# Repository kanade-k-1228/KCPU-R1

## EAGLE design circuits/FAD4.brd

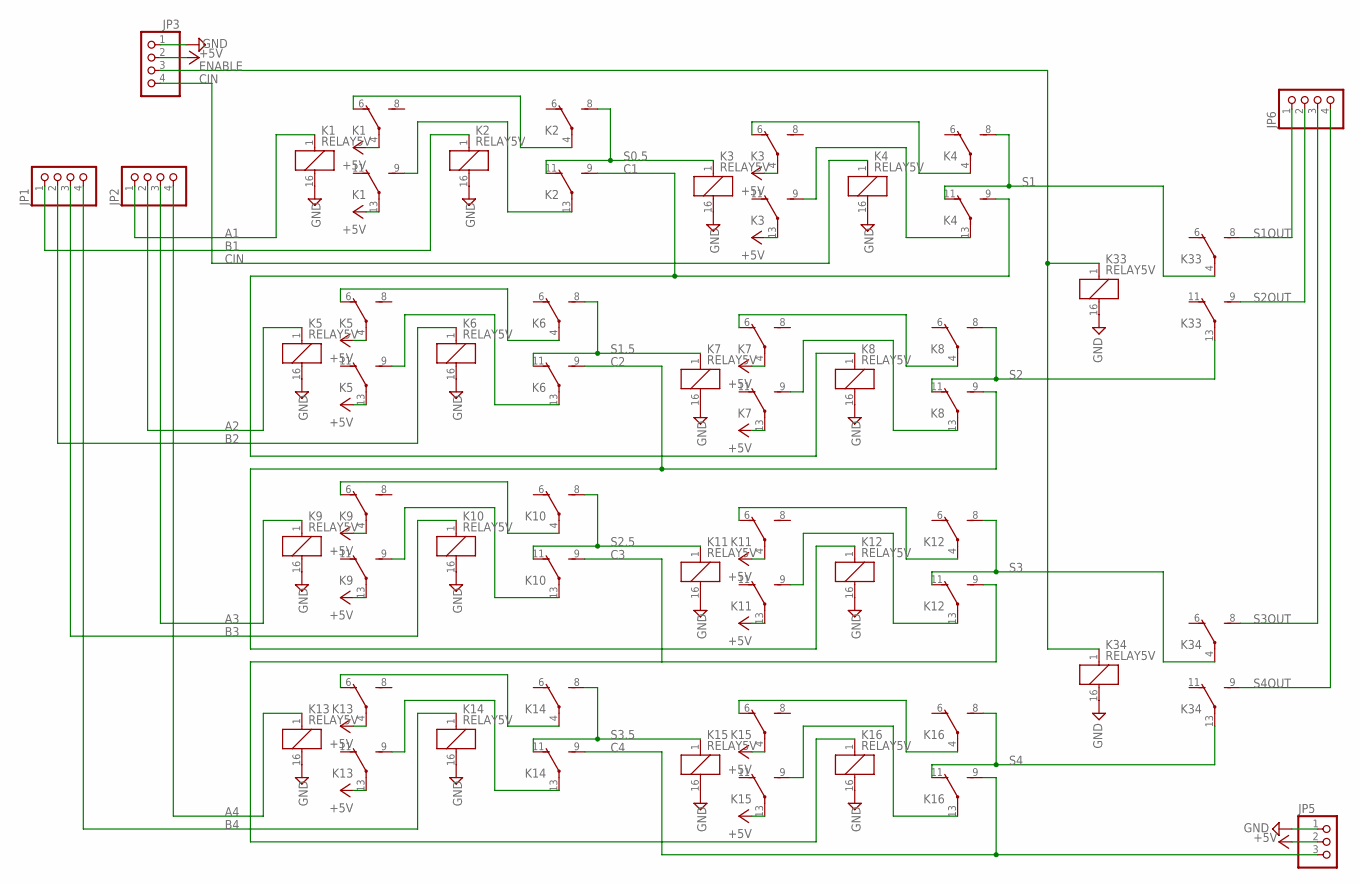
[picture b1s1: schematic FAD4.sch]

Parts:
JP1, JP2, JP3, JP6: PINHD-1X4; 1X04
JP5: PINHD-1X3; 1X03
K1, K2, K3, K4, K5, K6, K7, K8, K9, K10, K11, K12, K13, K14, K15, K16, K33, K34: RELAY5V; DS-BT

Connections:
+5V: JP3.2, JP5.2, K1.4, K1.13, K3.4, K3.13, K5.4, K5.13, K7.4, K7.13, K9.4, K9.13, K11.4, K11.13, K13.4, K13.13, K15.4, K15.13
A1: JP2.1, K1.1 (+)
A2: JP2.2, K5.1 (+)
A3: JP2.3, K9.1 (+)
A4: JP2.4, K13.1 (+)
B1: JP1.1, K2.1 (+)
B2: JP1.2, K6.1 (+)
B3: JP1.3, K10.1 (+)
B4: JP1.4, K14.1 (+)
C1: K2.9 (S), K4.9 (S), K8.1 (+)
C2: K6.9 (S), K8.9 (S), K12.1 (+)
C3: K10.9 (S), K12.9 (S), K16.1 (+)
C4: JP5.3, K14.9 (S), K16.9 (S)
CIN: JP3.4, K4.1 (+)
ENABLE: JP3.3, K33.1 (+), K34.1 (+)
GND: JP3.1, JP5.1, K1.16 (-), K2.16 (-), K3.16 (-), K4.16 (-), K5.16 (-), K6.16 (-), K7.16 (-), K8.16 (-), K9.16 (-), K10.16 (-), K11.16 (-), K12.16 (-), K13.16 (-), K14.16 (-), K15.16 (-), K16.16 (-), K33.16 (-), K34.16 (-)
unnamed: K3.9 (S), K4.13
unnamed: K1.9 (S), K2.13
unnamed: K1.6 (O), K2.4
unnamed: K3.6 (O), K4.4
unnamed: K5.9 (S), K6.13
unnamed: K5.6 (O), K6.4
unnamed: K7.9 (S), K8.13
unnamed: K7.6 (O), K8.4
unnamed: K9.9 (S), K10.13
unnamed: K9.6 (O), K10.4
unnamed: K11.9 (S), K12.13
unnamed: K11.6 (O), K12.4
unnamed: K13.9 (S), K14.13
unnamed: K13.6 (O), K14.4
unnamed: K15.9 (S), K16.13
unnamed: K15.6 (O), K16.4
S0.5: K2.8 (S), K2.11 (O), K3.1 (+)
S1: K4.8 (S), K4.11 (O), K33.4
S1.5: K6.8 (S), K6.11 (O), K7.1 (+)
S1OUT: JP6.1, K33.8 (S)
S2: K8.8 (S), K8.11 (O), K33.13
S2.5: K10.8 (S), K10.11 (O), K11.1 (+)
S2OUT: JP6.2, K33.9 (S)
S3: K12.8 (S), K12.11 (O), K34.4
S3.5: K14.8 (S), K14.11 (O), K15.1 (+)
S3OUT: JP6.3, K34.8 (S)
S4: K16.8 (S), K16.11 (O), K34.13
S4OUT: JP6.4, K34.9 (S)

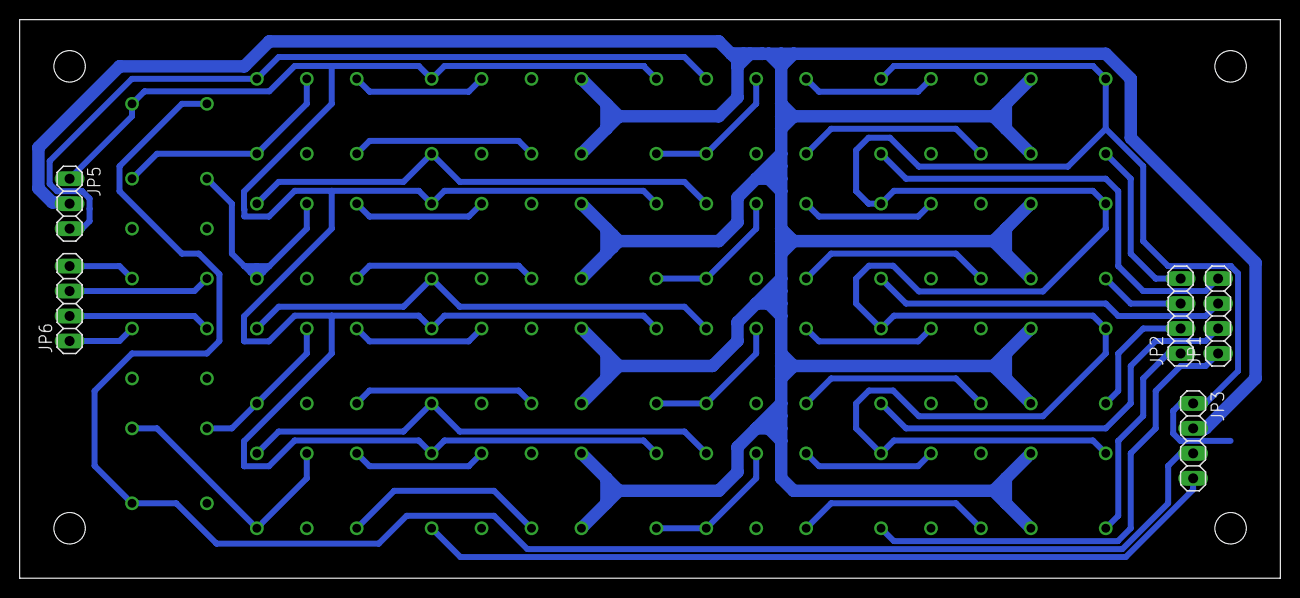
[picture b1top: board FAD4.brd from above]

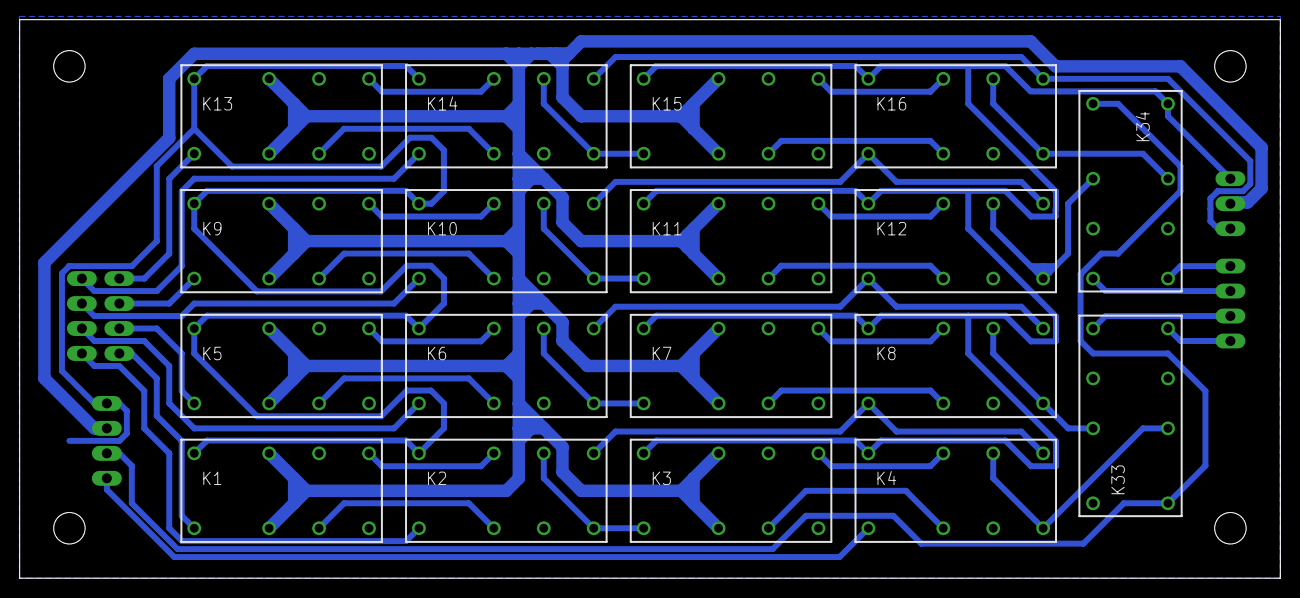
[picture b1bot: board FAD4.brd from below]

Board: 2 copper layers, 128.2 x 56.8 mm, 27 parts (18 on the bottom side), 44 nets.

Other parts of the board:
U$1, U$2, U$3, U$4: HOLE_3.2

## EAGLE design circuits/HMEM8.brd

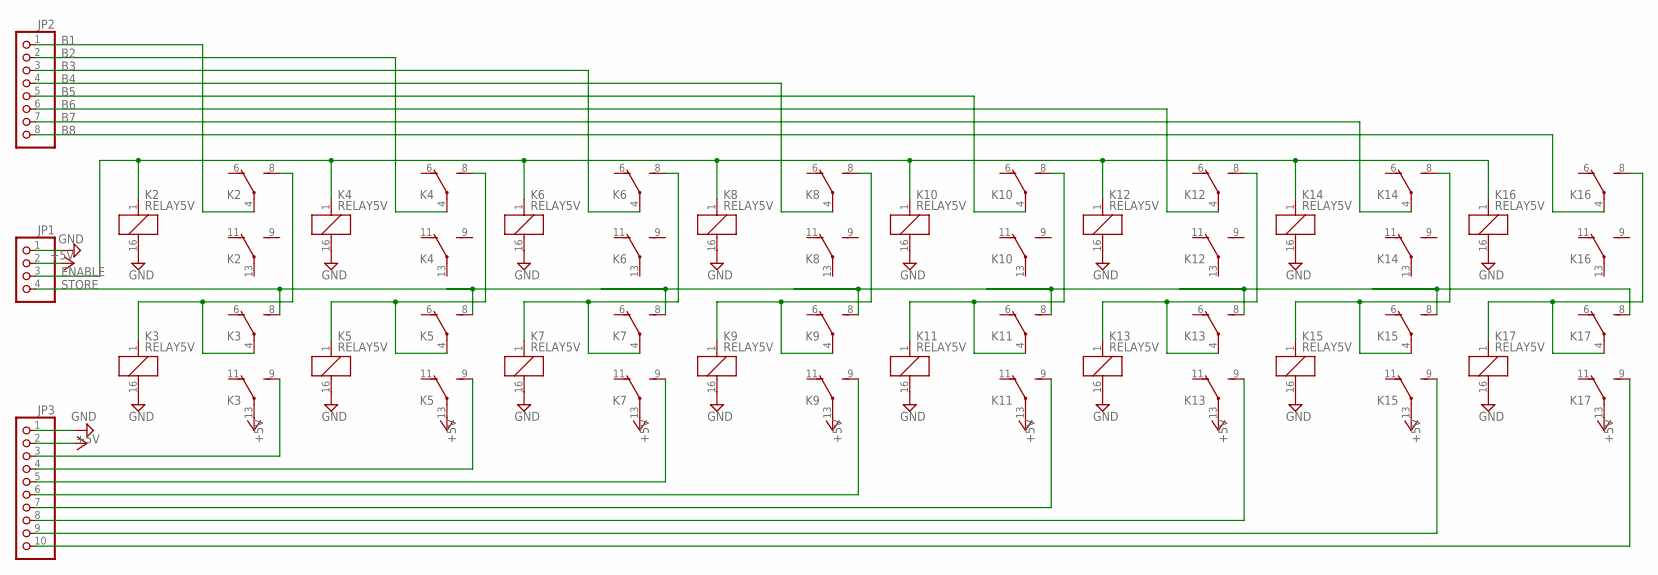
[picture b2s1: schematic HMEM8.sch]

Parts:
JP1: PINHD-1X4; 1X04
JP2: PINHD-1X8; 1X08
JP3: PINHD-1X10; 1X10
K2, K3, K4, K5, K6, K7, K8, K9, K10, K11, K12, K13, K14, K15, K16, K17: RELAY5V; DS-BT

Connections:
+5V: JP1.2, JP3.2, K3.13, K5.13, K7.13, K9.13, K11.13, K13.13, K15.13, K17.13
B1: JP2.1, K2.4
B2: JP2.2, K4.4
B3: JP2.3, K6.4
B4: JP2.4, K8.4
B5: JP2.5, K10.4
B6: JP2.6, K12.4
B7: JP2.7, K14.4
B8: JP2.8, K16.4
ENABLE: JP1.3, K2.1 (+), K4.1 (+), K6.1 (+), K8.1 (+), K10.1 (+), K12.1 (+), K14.1 (+), K16.1 (+)
GND: JP1.1, JP3.1, K2.16 (-), K3.16 (-), K4.16 (-), K5.16 (-), K6.16 (-), K7.16 (-), K8.16 (-), K9.16 (-), K10.16 (-), K11.16 (-), K12.16 (-), K13.16 (-), K14.16 (-), K15.16 (-), K16.16 (-), K17.16 (-)
unnamed: K2.8 (S), K3.1 (+), K3.4
unnamed: JP3.3, K3.9 (S)
unnamed: K4.8 (S), K5.1 (+), K5.4
unnamed: K6.8 (S), K7.1 (+), K7.4
unnamed: K8.8 (S), K9.1 (+), K9.4
unnamed: JP3.4, K5.9 (S)
unnamed: K10.8 (S), K11.1 (+), K11.4
unnamed: JP3.5, K7.9 (S)
unnamed: K12.8 (S), K13.1 (+), K13.4
unnamed: JP3.6, K9.9 (S)
unnamed: K14.8 (S), K15.1 (+), K15.4
unnamed: JP3.7, K11.9 (S)
unnamed: K16.8 (S), K17.1 (+), K17.4
unnamed: JP3.8, K13.9 (S)
unnamed: JP3.9, K15.9 (S)
unnamed: JP3.10, K17.9 (S)
STORE: JP1.4, K3.8 (S), K5.8 (S), K7.8 (S), K9.8 (S), K11.8 (S), K13.8 (S), K15.8 (S), K17.8 (S)

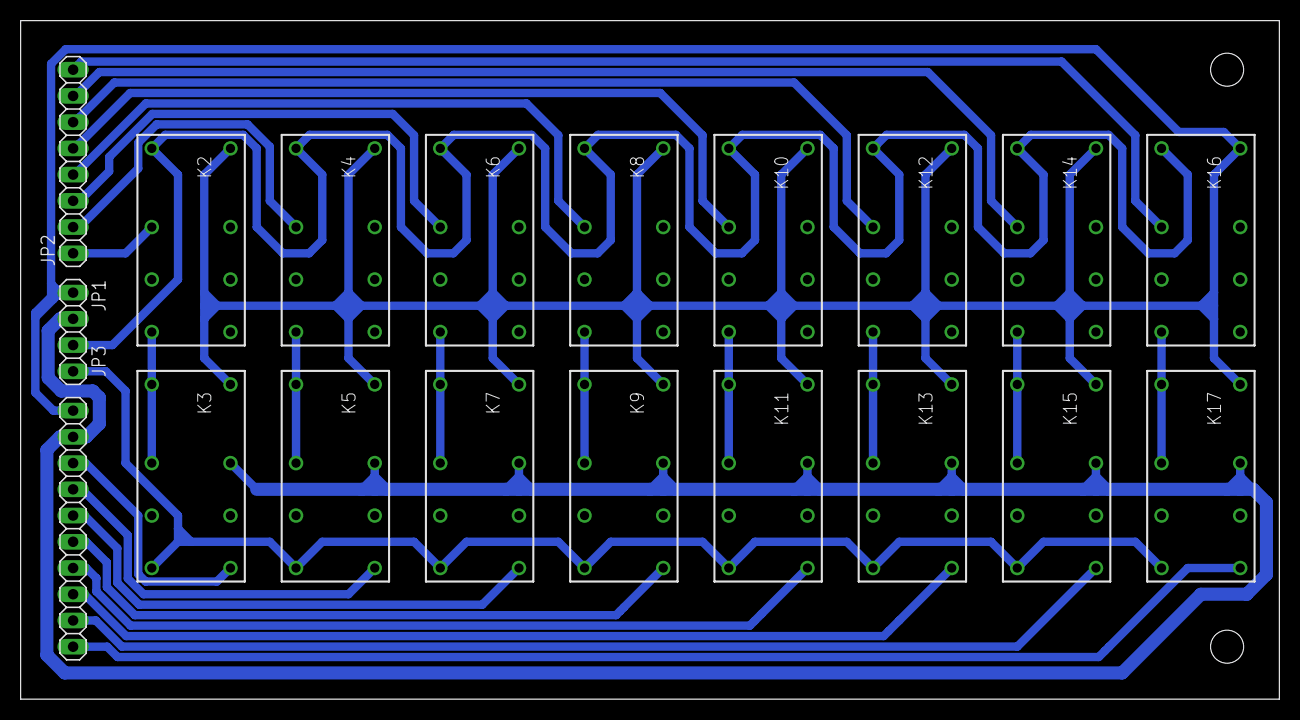
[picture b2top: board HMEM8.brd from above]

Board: 2 copper layers, 121.9 x 65.7 mm, 21 parts (0 on the bottom side), 28 nets.

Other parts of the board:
U$1, U$2: HOLE_3.2

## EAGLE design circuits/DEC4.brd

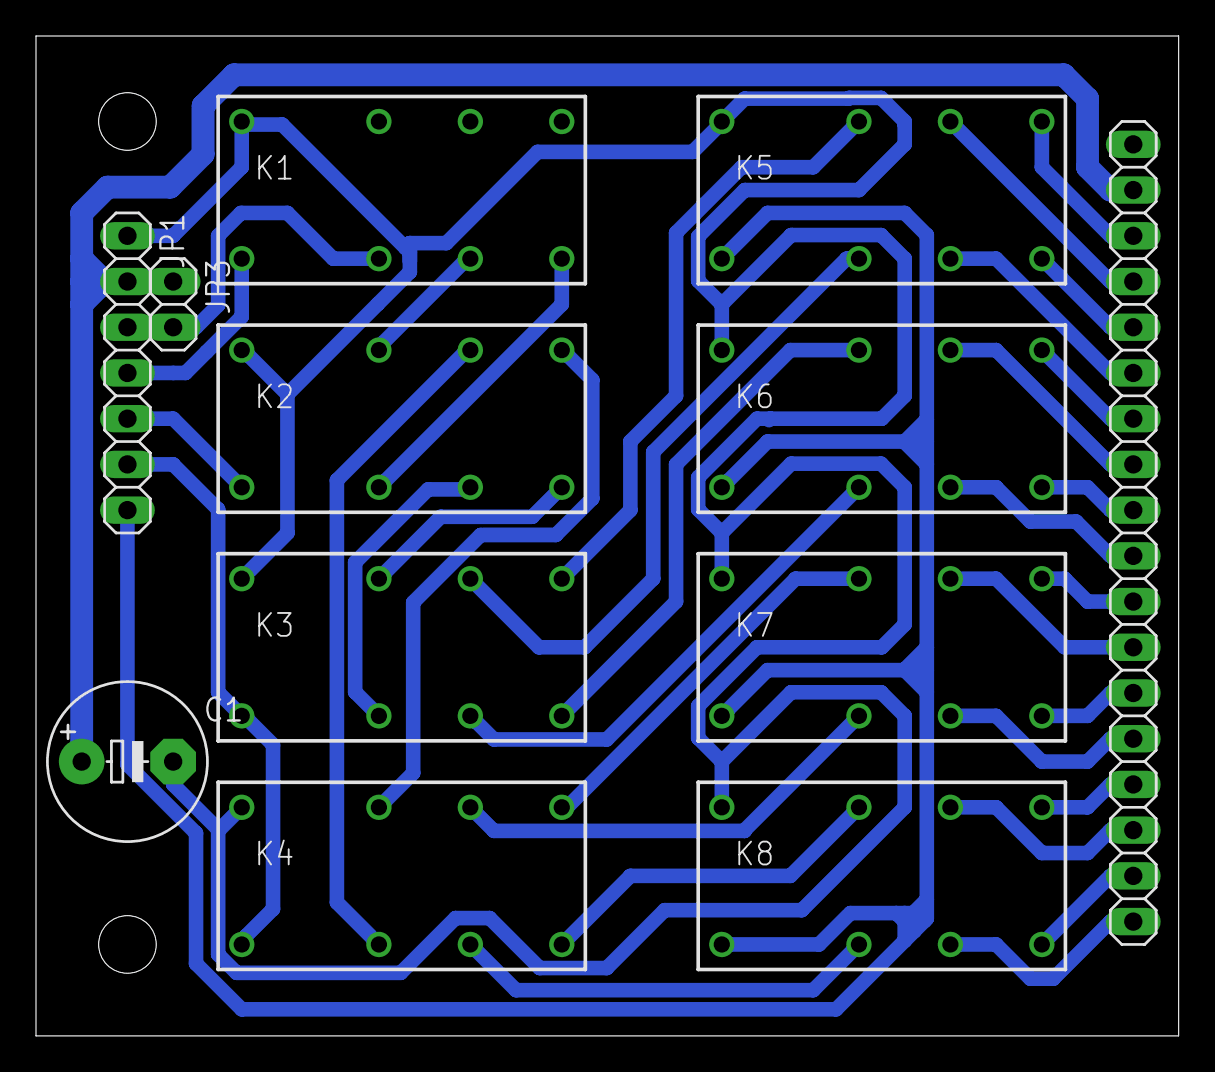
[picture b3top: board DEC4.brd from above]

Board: 2 copper layers, 63.5 x 55.5 mm, 14 parts (0 on the bottom side), 37 nets.

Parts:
C1: E5-8,5
JP1: 1X07
JP2: 1X18
JP3: 1X02
K1, K2, K3, K4, K5, K6, K7, K8: RELAY5V; DS-BT
U$1, U$2: HOLE_3.2

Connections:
+5V: C1.+, JP1.2, JP2.2, JP3.1
GND: C1.-, JP1.1, JP2.1, K1.16, K2.16, K3.16, K4.16, K5.16, K6.16, K7.16, K8.16
unnamed: K1.8, K2.4
unnamed: K1.6, K2.13
unnamed: K2.8, K3.13
unnamed: K2.6, K3.4
unnamed: K2.9, K4.13
unnamed: K2.11, K4.4
unnamed: K3.9, K5.13
unnamed: K3.11, K5.4
unnamed: K3.8, K6.13
unnamed: K3.6, K6.4
unnamed: K4.9, K7.13
unnamed: K4.11, K7.4
unnamed: K4.8, K8.13
unnamed: K4.6, K8.4
unnamed: JP2.3, K5.9
unnamed: JP1.6, K3.1, K4.1
unnamed: JP1.7, K5.1, K6.1, K7.1, K8.1
unnamed: JP2.4, K5.11
unnamed: JP1.4, K1.1
unnamed: JP1.5, K2.1
unnamed: JP2.5, K5.8
unnamed: JP2.6, K5.6
unnamed: JP2.7, K6.9
unnamed: JP2.8, K6.11
unnamed: JP2.9, K6.8
unnamed: JP2.10, K6.6
unnamed: JP2.11, K7.9
unnamed: JP2.12, K7.11
unnamed: JP2.13, K7.8
unnamed: JP2.14, K7.6
unnamed: JP2.15, K8.9
unnamed: JP2.16, K8.11
unnamed: JP2.17, K8.8
unnamed: JP2.18, K8.6
unnamed: JP1.3, JP3.2, K1.4

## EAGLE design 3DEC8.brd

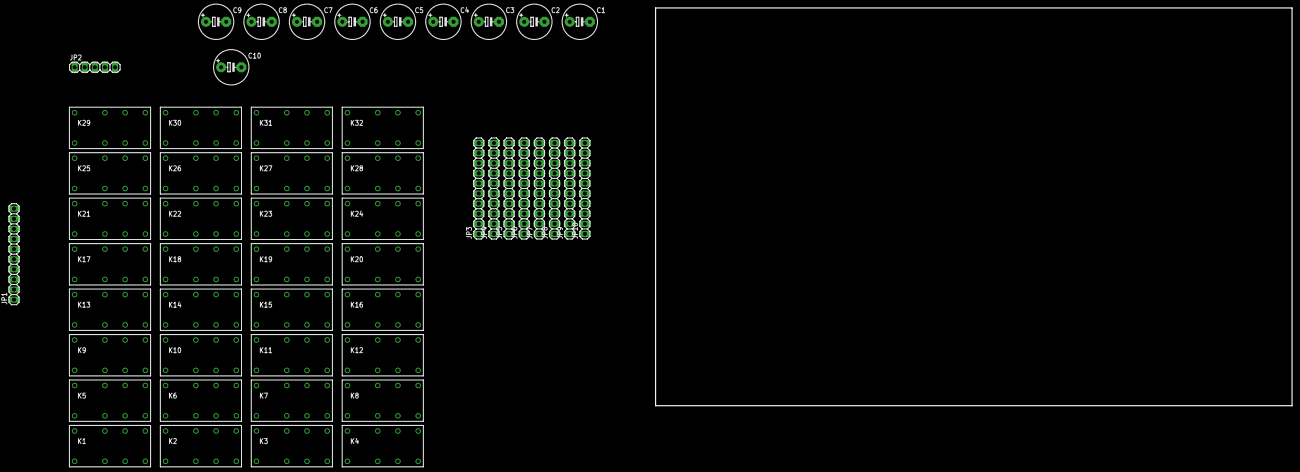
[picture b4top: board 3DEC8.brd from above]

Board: 2 copper layers, 160.0 x 100.0 mm, 52 parts (0 on the bottom side), 87 nets, no tracks yet.

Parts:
C1, C2, C3, C4, C5, C6, C7, C8, C9, C10: E5-8,5
JP1, JP3, JP4, JP5, JP6, JP7, JP8, JP9, JP10: 1X10
JP2: 1X05
K1, K2, K3, K4, K5, K6, K7, K8, K9, K10, K11, K12, K13, K14, K15, K16, K17, K18, K19, K20, K21, K22, K23, K24, K25, K26, K27, K28, K29, K30, K31, K32: RELAY5V; DS-BT

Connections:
+5V: C1.+, C2.+, C3.+, C4.+, C5.+, C6.+, C7.+, C8.+, C9.+, C10.+, JP1.2, JP2.2, JP3.2, JP4.2, JP5.2, JP6.2, JP7.2, JP8.2, JP9.2, JP10.2
GND: C1.-, C2.-, C3.-, C4.-, C5.-, C6.-, C7.-, C8.-, C9.-, C10.-, JP1.1, JP2.1, JP3.1, JP4.1, JP5.1, JP6.1, JP7.1, JP8.1, JP9.1, JP10.1, K1.16, K2.16, K3.16, K4.16, K5.16, K6.16, K7.16, K8.16, K9.16, K10.16, K11.16, K12.16, K13.16, K14.16, K15.16, K16.16, K17.16, K18.16, K19.16, K20.16, K21.16, K22.16, K23.16, K24.16, K25.16, K26.16, K27.16, K28.16, K29.16, K30.16, K31.16, K32.16
unnamed: K1.8, K2.4
unnamed: K1.6, K2.13
unnamed: K2.8, K3.13
unnamed: K2.6, K3.4
unnamed: K2.9, K4.13
unnamed: K2.11, K4.4
unnamed: JP10.3, K3.9
unnamed: K5.8, K6.4
unnamed: JP9.3, K3.11
unnamed: JP7.3, K3.6
unnamed: K5.6, K6.13
unnamed: JP5.3, K4.11
unnamed: JP4.4, K8.8
unnamed: JP4.3, K4.8
unnamed: JP8.3, K3.8
unnamed: JP4.5, K12.8
unnamed: JP6.3, K4.9
unnamed: K6.8, K7.13
unnamed: JP2.3, K1.1, K5.1, K9.1, K13.1, K17.1, K21.1, K25.1, K29.1
unnamed: JP2.4, K2.1, K6.1, K10.1, K14.1, K18.1, K22.1, K26.1, K30.1
unnamed: K6.6, K7.4
unnamed: K6.9, K8.13
unnamed: K6.11, K8.4
unnamed: JP7.4, K7.6
unnamed: JP5.4, K8.11
unnamed: JP3.4, K8.6
unnamed: JP1.4, K5.4
unnamed: JP9.4, K7.11
unnamed: JP3.3, K4.6
unnamed: JP8.4, K7.8
unnamed: JP6.4, K8.9
unnamed: JP1.3, K1.4
unnamed: JP10.4, K7.9
unnamed: K9.8, K10.4
unnamed: K9.6, K10.13
unnamed: K10.8, K11.13
unnamed: K10.6, K11.4
unnamed: K10.9, K12.13
unnamed: K10.11, K12.4
unnamed: JP7.5, K11.6
unnamed: JP5.5, K12.11
unnamed: JP3.5, K12.6
unnamed: JP2.5, K3.1, K4.1, K7.1, K8.1, K11.1, K12.1, K15.1, K16.1, K19.1, K20.1, K23.1, K24.1, K27.1, K28.1, K31.1, K32.1
unnamed: JP1.5, K9.4
unnamed: JP6.5, K12.9
unnamed: K13.8, K14.4
unnamed: K13.6, K14.13
unnamed: K14.8, K15.13
unnamed: K14.6, K15.4
unnamed: K14.9, K16.13
unnamed: K14.11, K16.4
unnamed: JP3.6, K16.6
unnamed: JP1.6, K13.4
unnamed: K17.8, K18.4
unnamed: K17.6, K18.13
unnamed: K18.8, K19.13
unnamed: K18.6, K19.4
unnamed: K18.9, K20.13
unnamed: K18.11, K20.4
unnamed: JP3.7, K20.6
unnamed: JP1.7, K17.4
unnamed: K21.8, K22.4
unnamed: K21.6, K22.13
unnamed: K22.8, K23.13
unnamed: K22.6, K23.4
unnamed: K22.9, K24.13
unnamed: K22.11, K24.4
unnamed: JP3.8, K24.6
unnamed: JP1.8, K21.4
unnamed: K25.8, K26.4
unnamed: K25.6, K26.13
unnamed: K26.8, K27.13
unnamed: K26.6, K27.4
unnamed: K26.9, K28.13
unnamed: K26.11, K28.4
unnamed: JP3.9, K28.6
unnamed: JP1.9, K25.4
unnamed: K29.8, K30.4
unnamed: K29.6, K30.13
unnamed: K30.8, K31.13
unnamed: K30.6, K31.4
unnamed: K30.9, K32.13
unnamed: K30.11, K32.4
unnamed: JP3.10, K32.6
unnamed: JP1.10, K29.4

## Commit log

2019-12-03 Copy
2019-12-03 hoge
2019-12-10 命令セット
